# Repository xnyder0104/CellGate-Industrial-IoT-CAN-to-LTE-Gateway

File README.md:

# CellGate: Industrial IoT CAN-to-LTE Gateway

## Project Overview

This project is a compact, reliable, and manufacturable 2-layer custom PCB designed to bridge physical CAN bus networks with cloud infrastructure via cellular telemetry. Operating in harsh embedded environments, such as automotive engine bays or industrial factory floors, requires highly robust hardware. Power fluctuations, electrical noise, and Electrostatic Discharge (ESD) events can easily destroy standard development boards or cause critical communication failures.

To overcome these challenges, CellGate utilizes an STM32 ARM Cortex-M0+ microcontroller paired with a Quectel EC200U LTE Cat-1 module to handle high-speed data processing and transmission. The board integrates an industrial power path, strictly isolated voltage domains, multi-stage hardware protection, and a seamless load-sharing battery backup system, ensuring uninterrupted diagnostic data flow.

## Key Features & Engineering Highlights

* **Advanced Power Path Management:** Implements a PMV65XP MOSFET-based load-sharing architecture that automatically and seamlessly switches between a high-voltage external DC input (up to 40V) and a Lithium-ion battery backup without resetting the system.
* **Strict Voltage Domain Isolation:** A TXB0104 bidirectional logic level shifter protects the sensitive 1.8V Quectel silicon from the 3.3V STM32 logic signals, enabling safe, high-speed full-duplex UART transmission.
* **Fail-Safe Boot Design:** Integrates a hardware-level 10k-ohm pull-down resistor on the STM32 BOOT0 (PA14) pin to prevent the MCU from accidentally entering DFU Bootloader Mode due to ambient electrical noise during battery-only field operation.
* **Multi-Stage ESD Armor:** Deploys hardware protection across all external interfaces, including PESD2CAN TVS diodes on the differential bus lines and USBLC6 protection on the Type-C port.
* **Selectable Bus Termination:** Includes a physical jumper header for selectable 120-ohm CAN bus termination, making the board adaptable for end-of-line or mid-bus installations.
* **Comprehensive Diagnostic UI:** A dedicated 9-LED onboard panel provides immediate visual debugging for Main Power, Battery Charging, Battery Full, MCU Status, LTE Network Status, GPS Fix, CAN Activity, UART Activity, and Hardware Errors/Faults.

## Hardware Architecture & Working Principle

### 1. Power Supply & Battery Protection (+V_SYS)
* **HV Step-Down:** An LMR14030 buck converter steps down raw industrial inputs (up to 40V) to a stable 5V rail.
* **Voltage Regulation:** The master +V_SYS net feeds two independent LDOs: an AMS1117 generating the 3.3V MCU domain, and a TLV70218 generating the 1.8V modem reference domain.
* **Battery Circuitry:** A TP4056 linear charger manages Li-ion charging. It is paired with a strictly low-side DW01A controller and dual FS8205A MOSFETs, which continuously monitor the cell and isolate the battery ground instantly if over-charge, over-discharge, or a dead-short is detected.

### 2. Core Processing & Connectivity
* **Microcontroller Logic:** The STM32G0B1CBT6 handles all data preprocessing, CAN-to-UART conversion, and LED status mapping. 
* **Cellular & GNSS:** The Quectel EC200U module executes AT commands for LTE telemetry and GNSS location tracking. It is powered directly from the high-current battery rail (+V_BAT) to sustain 2-Amp transmission bursts safely.
* **CAN Interface:** An SN65HVD230 transceiver safely translates high-voltage automotive differential CAN signals down to the 3.3V logic level required by the STM32.

### 3. Debugging & Firmware Interfaces
* **SWD Programming:** Standard 5-pin SWD interface (SWDIO, SWCLK, NRST, +3.3V, GND) for flashing the STM32.
* **Hardware UART:** An exposed 4-pin hardware UART header operating strictly at 1.8V (VDD_EXT) for direct, low-level Quectel modem diagnostics.
* **USB Type-C:** Directly exposes the EC200U USB interface for cellular firmware upgrades and advanced module diagnostics.

## PCB Layout & Manufacturing Strategy

The board was meticulously routed as a 2-layer PCB, optimizing for low parasitic inductance, signal integrity, and manufacturability:

* **Solid Ground Plane:** The entire bottom layer is maintained as an unbroken solid copper ground plane to absorb the massive switching noise of the LMR14030 buck converter and provide a clean return path for RF signals.
* **Bottom-Layer Decoupling:** To minimize trace length and parasitic inductance, critical decoupling capacitors for the STM32 and Quectel EC200U are placed directly underneath the component pins on the bottom layer, fed by localized via stitching.
* **45-Degree Mitered Routing:** All high-speed data lines (6-mil trace width) utilize clean 45-degree cornering, avoiding 90-degree right angles and acute acid traps to ensure perfect chemical etching during manufacturing.
* **RF Trace Geometry:** 50-ohm controlled impedance traces are routed cleanly from the modem RF pads directly to the U.FL edge connectors, completely avoiding vias to prevent signal reflection.

## Applications

* Heavy machinery and fleet management telemetry (CAN bus diagnostics).
* Remote industrial equipment monitoring and predictive maintenance.
* Standalone IoT sensor gateways for off-grid environmental tracking.
* High-reliability telemetry nodes requiring uninterruptible power supplies (UPS).

## Future Scope

* **Mechanical Enclosure Design:** Utilizing the exported 3D .step files to design a custom, IP67-rated waterproof housing for harsh outdoor deployments.
* **Firmware Over-The-Air (FOTA):** Implementing a custom MCU bootloader to download, verify, and flash firmware updates seamlessly via the Quectel LTE connection.
* **Onboard Sensor Expansion:** Integrating standard I2C/SPI environmental sensors (e.g., temperature, humidity, accelerometer) directly onto the motherboard for localized physical diagnostics.

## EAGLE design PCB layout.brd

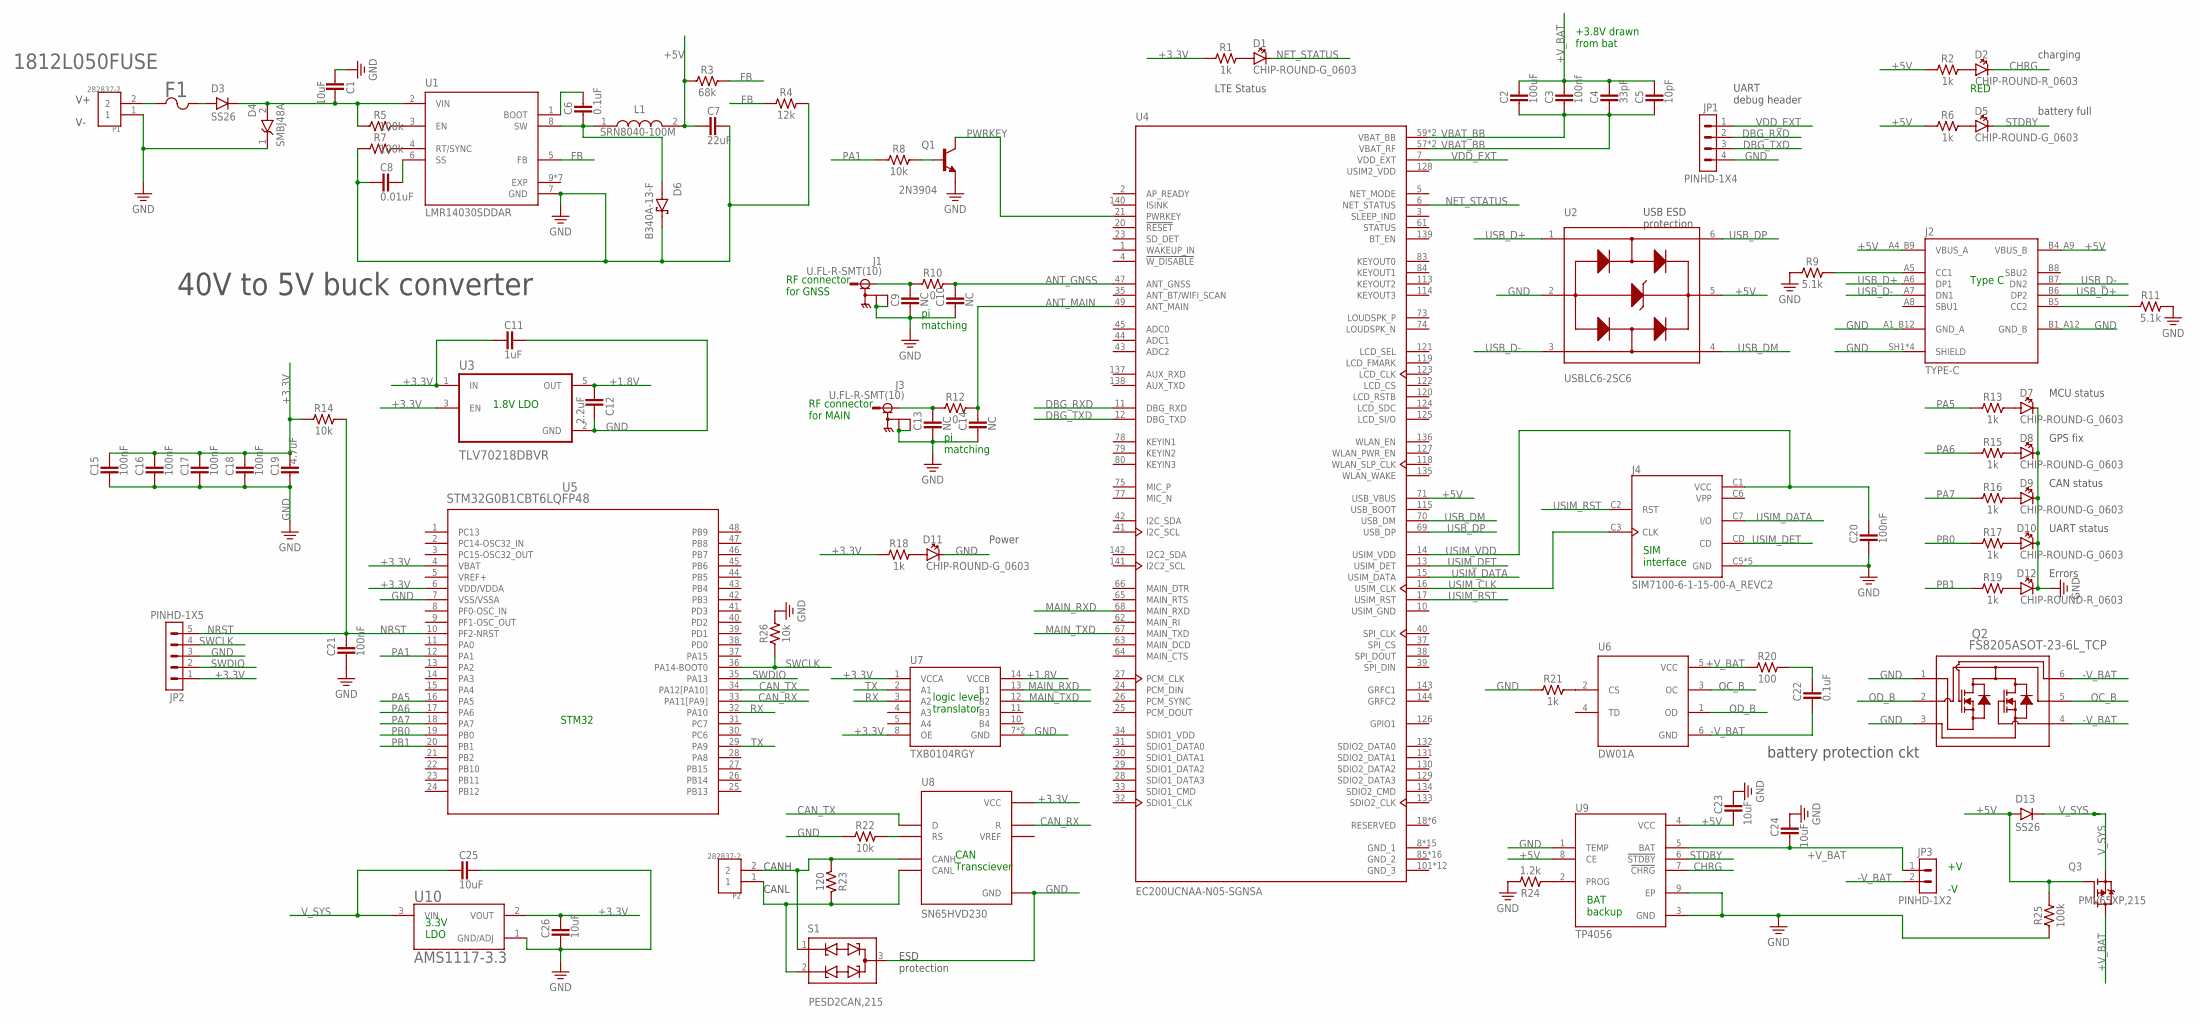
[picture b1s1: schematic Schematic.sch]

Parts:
C1, C23, C24, C25, C26: 10uF; CAPC1005X60
C2: 100uF; CAPC1608X85
C3: 100nf; CAPC1608X85
C4: 33pF; CAPC1608X85
C5: 10pF; CAPC1608X85
C6, C22: 0.1uF; CAPC1005X60
C7: 22uF; CAPC1005X60
C8: 0.01uF; CAPC1005X60
C9, C10, C13, C14: NC; CAPC1005X60
C11: 1uF; CAPC1005X60
C12: 2.2uF; CAPC1005X60
C15, C16, C17, C18, C20, C21: 100nF; CAPC1005X60
C19: 4.7uF; CAPC1005X60
D1, D5, D7, D8, D9, D10, D11: CHIP-ROUND-G_0603; LEDC1608X65N_RND-G
D2, D12: CHIP-ROUND-R_0603; LEDC1608X65N_RND-R
D3, D13: SS26
D4: SMBJ48A; DIOM5436X261N
D6: B340A-13-F; DIOM5226X240N
F1: 1812L050FUSE; FUSE_1812L05060_LTF
J1, J3: U.FL-R-SMT(10); HIROSE_U.FL-R-SMT(10)
J2: TYPE-C; SHOUHAN_TYPE-C_16PIN_2MD_(073)
J4: SIM7100-6-1-15-00-A_REVC2; GCT_SIM7100-6-1-15-00-A_REVC2
JP1: PINHD-1X4; 1X04
JP2: PINHD-1X5; 1X05
JP3: PINHD-1X2; 1X02
L1: SRN8040-100M; SRN8040100M
P1, P2: 282837-2; TE_282837-2
Q1: 2N3904; TO92127P495H495-3
Q2: FS8205ASOT-23-6L_TCP; SOT-23-6L_TCP
Q3: PMV65XP,215; SOT95P230X110-3N
R1, R2, R6, R13, R15, R16, R17, R18, R19, R21: 1k; RESC1005X40
R3: 68k; RESC1005X40
R4: 12k; RESC1005X40
R5, R7, R25: 100k; RESC1005X40
R8, R14, R22, R26: 10k; RESC1005X40
R9, R11: 5.1k; RESC1005X40
R10, R12: 0; RESC1005X40
R20: 100; RESC1005X40
R23: 120; RESC1005X40
R24: 1.2k; RESC1005X40
S1: PESD2CAN,215; DIO_PESD2CAN,215
U1: LMR14030SDDAR; SOIC127P600X170-9N
U2: USBLC6-2SC6; SOT95P280X145-6N
U3: TLV70218DBVR; SOT95P280X145-5N
U4: EC200UCNAA-N05-SGNSA; XCVR_EC200UCNAA-N05-SGNSA
U5: STM32G0B1CBT6LQFP48; LQFP48_STM32G0B1CBT_STM
U6: DW01A; SOT95P280X145-6N
U7: TXB0104RGY; S-PVQFN-N14
U8: SN65HVD230; SOIC127P599X175-8N
U9: TP4056; SOP127P600X175-9N
U10: AMS1117-3.3; SOT229P700X180-4N

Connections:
+1.8V: C12.2, U3.5 (OUT), U7.14 (VCCB)
+3.3V: C11.2, C15.1, C16.1, C17.1, C18.1, C19.1, C26.1, JP2.1, R1.1, R14.1, R18.1, U3.1 (IN), U3.3 (EN), U5.4 (VBAT), U5.6 (VDD/VDDA), U7.1 (VCCA), U7.8 (OE), U8.3 (VCC), U10.2 (VOUT)
+5V: C7.2, C23.2, D13.A, J2.A4_B9 (VBUS_A), J2.B4_A9 (VBUS_B), L1.2, Q3.1 (G), R2.1, R3.1, R6.1, R25.2, U2.5 (VBUS), U4.71 (USB_VBUS), U9.4 (VCC), U9.8 (CE)
+V_BAT: C2.1, C3.1, C4.1, C5.1, C24.2, JP3.1, Q3.3 (D), R20.1, U6.5 (VCC), U9.5 (BAT)
-V_BAT: C22.2, JP3.2, Q2.4, Q2.6, U6.6 (GND)
ANT_GNSS: C10.1, R10.2, U4.47 (ANT_GNSS)
ANT_MAIN: C14.1, R12.2, U4.49 (ANT_MAIN)
CANH: P2.2, R23.2, S1.1 (C1), U8.7 (CANH)
CAN_RX: U5.33 (PA11[PA9]), U8.4 (R)
CAN_TX: U5.34 (PA12[PA10]), U8.1 (D)
CHRG: D2.C, U9.7 (!CHRG)
DBG_RXD: JP1.2, U4.11 (DBG_RXD)
DBG_TXD: JP1.3, U4.12 (DBG_TXD)
EXP: U1.9 (EXP), U1.V1 (EXP), U1.V2 (EXP), U1.V3 (EXP), U1.V4 (EXP), U1.V5 (EXP), U1.V6 (EXP)
FB: R3.2, R4.1, U1.5 (FB)
GND: C1.2, C7.1, C8.2, C9.2, C10.2, C11.1, C12.1, C13.2, C14.2, C15.2, C16.2, C17.2, C18.2, C19.2, C20.2, C21.2, C23.1, C24.1, C25.1, C26.2, D4.1 (K), D6.C, D7.C, D8.C, D9.C, D10.C, D11.C, D12.C, J1.G1, J1.G2, J2.A1_B12 (GND_A), J2.B1_A12 (GND_B), J2.SH1 (SHIELD), J2.SH2 (SHIELD), J2.SH3 (SHIELD), J2.SH4 (SHIELD), J3.G1, J3.G2, J4.C5 (GND), J4.G1 (GND), J4.G2 (GND), J4.G3 (GND), J4.G4 (GND), JP1.4, JP2.3, P1.1, Q1.1 (E), Q2.1, Q2.3, R4.2, R7.1, R9.1, R11.2, R21.1, R22.1, R24.2, R25.1, R26.2, S1.3 (CC), U1.7 (GND), U2.2 (GND), U3.2 (GND), U5.7 (VSS/VSSA), U7.7 (GND), U7.THERMALPAD (GND), U8.2 (GND), U9.1 (TEMP), U9.3 (GND), U9.9 (EP), U10.1 (GND/ADJ)
GND_1: U4.8 (GND_1), U4.9 (GND_1), U4.19 (GND_1), U4.22 (GND_1), U4.36 (GND_1), U4.46 (GND_1), U4.48 (GND_1), U4.50 (GND_1), U4.51 (GND_1), U4.52 (GND_1), U4.53 (GND_1), U4.54 (GND_1), U4.56 (GND_1), U4.72 (GND_1), U4.76 (GND_1)
GND_2: U4.85 (GND_2), U4.86 (GND_2), U4.87 (GND_2), U4.88 (GND_2), U4.89 (GND_2), U4.90 (GND_2), U4.91 (GND_2), U4.92 (GND_2), U4.93 (GND_2), U4.94 (GND_2), U4.95 (GND_2), U4.96 (GND_2), U4.97 (GND_2), U4.98 (GND_2), U4.99 (GND_2), U4.100 (GND_2)
GND_3: U4.101 (GND_3), U4.102 (GND_3), U4.103 (GND_3), U4.104 (GND_3), U4.105 (GND_3), U4.106 (GND_3), U4.107 (GND_3), U4.108 (GND_3), U4.109 (GND_3), U4.110 (GND_3), U4.111 (GND_3), U4.112 (GND_3)
MAIN_RXD: U4.68 (MAIN_RXD), U7.13 (B1)
MAIN_TXD: U4.67 (MAIN_TXD), U7.12 (B2)
unnamed: Q1.2 (B), R8.2
unnamed: J2.A5 (CC1), R9.2
unnamed: J2.B5 (CC2), R11.1
unnamed: C9.1, J1.SIG, R10.1
unnamed: R24.1, U9.2 (PROG)
unnamed: D2.A, R2.2
unnamed: D5.A, R6.2
unnamed: C13.1, J3.SIG, R12.1
unnamed: R22.2, U8.8 (RS)
unnamed: F1.1, P1.2
unnamed: D3.A, F1.2
unnamed: C1.1, D3.C, D4.2 (A), R5.1, U1.2 (VIN)
unnamed: C6.1, U1.1 (BOOT)
unnamed: C6.2, D6.A, L1.1, U1.8 (SW)
unnamed: R5.2, U1.3 (EN)
unnamed: R7.2, U1.4 (RT/SYNC)
unnamed: C8.1, U1.6 (SS)
unnamed: R21.2, U6.2 (CS)
unnamed: D11.A, R18.2
unnamed: C22.1, R20.2
unnamed: P2.1, R23.1, S1.2 (C2), U8.6 (CANL)
unnamed: D1.A, R1.2
unnamed: D7.A, R13.2
unnamed: D8.A, R15.2
unnamed: D9.A, R16.2
unnamed: D10.A, R17.2
unnamed: D12.A, R19.2
NET_STATUS: D1.C, U4.6 (NET_STATUS)
NRST: C21.1, JP2.5, R14.2, U5.10 (PF2-NRST)
OC_B: Q2.5, U6.3 (OC)
OD_B: Q2.2, U6.1 (OD)
PA1: R8.1, U5.12 (PA1)
PA5: R13.1, U5.16 (PA5)
PA6: R15.1, U5.17 (PA6)
PA7: R16.1, U5.18 (PA7)
PB0: R17.1, U5.19 (PB0)
PB1: R19.1, U5.20 (PB1)
PWRKEY: Q1.3 (C), U4.21 (PWRKEY)
RX: U5.32 (PA10), U7.3 (A2)
SDIO1_VDD: U4.34 (SDIO1_VDD)
STDBY: D5.C, U9.6 (!STDBY)
SWCLK: JP2.4, R26.1, U5.36 (PA14-BOOT0)
SWDIO: JP2.2, U5.35 (PA13)
TX: U5.29 (PA9), U7.2 (A1)
USB_D+: J2.A6 (DP1), J2.B6 (DP2), U2.1 (I/O1_IN)
USB_D-: J2.A7 (DN1), J2.B7 (DN2), U2.3 (I/O2_IN)
USB_DM: U2.4 (I/O2_OUT), U4.70 (USB_DM)
USB_DP: U2.6 (I/O1_OUT), U4.69 (USB_DP)
USIM2_VDD: U4.128 (USIM2_VDD)
USIM_CLK: J4.C3 (CLK), U4.16 (USIM_CLK)
USIM_DATA: J4.C7 (I/O), U4.15 (USIM_DATA)
USIM_DET: J4.CD, U4.13 (USIM_DET)
USIM_GND: U4.10 (USIM_GND)
USIM_RST: J4.C2 (RST), U4.17 (USIM_RST)
USIM_VDD: C20.1, J4.C1 (VCC), U4.14 (USIM_VDD)
VBAT_BB: C2.2, C3.2, C4.2, C5.2, U4.57 (VBAT_RF), U4.58 (VBAT_RF), U4.59 (VBAT_BB), U4.60 (VBAT_BB)
VDD_EXT: JP1.1, U4.7 (VDD_EXT)
VPP: J4.C6 (VPP)
VREF+: U5.5 (VREF+)
V_SYS: C25.2, D13.C, Q3.2 (S), U10.3 (VIN)

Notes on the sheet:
1.8V LDO
logic level translator
CAN Transciever
STM32
Type C
RF connector for GNSS
pi matching
SIM interface
BAT backup
RED
RF connector for MAIN
+3.8V drawn from bat
3.3V LDO
ESD protection
40V to 5V buck converter
battery protection ckt
CANH
CANL
USB ESD protection
charging
battery full
Power
LTE Status
MCU status
GPS fix
CAN status
UART status
Errors
UART debug header

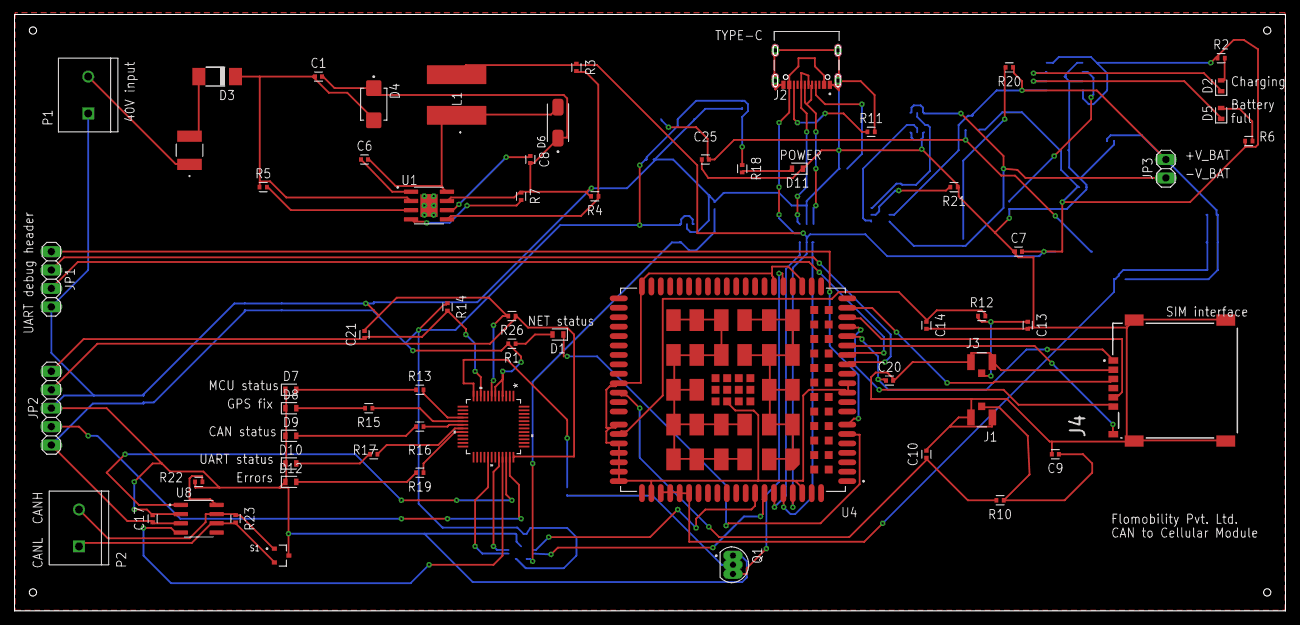
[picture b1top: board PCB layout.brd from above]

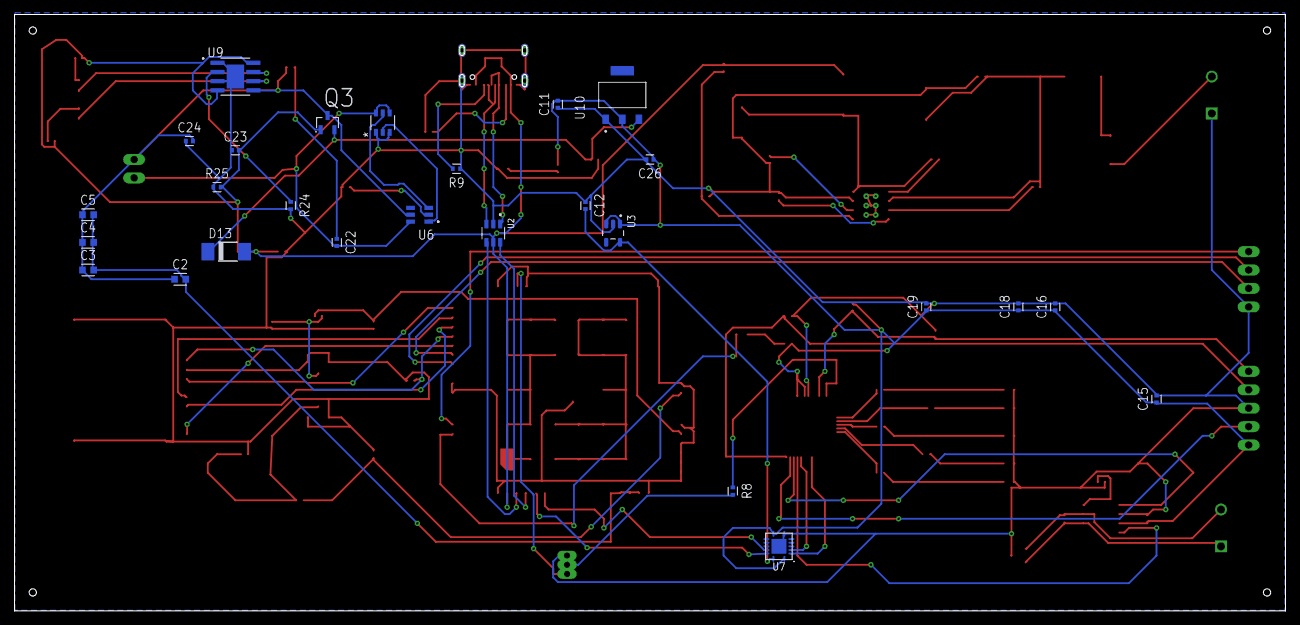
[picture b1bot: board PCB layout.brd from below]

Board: 2 copper layers, 175.2 x 82.2 mm, 90 parts (27 on the bottom side), 76 nets.

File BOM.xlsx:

Reference Designators | Quantity | Description | Package | Value | Top/Bottom
 | 1 | Board | Board
C1, C25 | 2 | Capacitor - Generic | CAPC1005X60 | 10uF | Top
C23, C24, C26 | 3 | Capacitor - Generic | CAPC1005X61 | 10uF | Bottom
C2 | 1 | Capacitor - Generic | CAPC1608X85 | 100uF | Bottom
C3 | 1 | Capacitor - Generic | CAPC1608X85 | 100nf | Bottom
C4 | 1 | Capacitor - Generic | CAPC1608X85 | 33pF | Bottom
C5 | 1 | Capacitor - Generic | CAPC1608X85 | 10pF | Bottom
C22 | 1 | Capacitor - Generic | CAPC1005X60 | 0.1uF | Bottom
C6 | 1 | Capacitor - Generic | CAPC1005X60 | 0.1uF | Top
C7 | 1 | Capacitor - Generic | CAPC1005X60 | 22uF | Top
C8 | 1 | Capacitor - Generic | CAPC1005X60 | 0.01uF | Top
C9, C10, C13, C14 | 4 | Capacitor - Generic | CAPC1005X60 | NC | Top
C11 | 1 | Capacitor - Generic | CAPC1005X60 | 1uF | Bottom
C12 | 1 | Capacitor - Generic | CAPC1005X60 | 2.2uF | Bottom
C15, C16, C18 | 3 | Capacitor - Generic | CAPC1005X60 | 100nF | Bottom
C17, C20, C21 | 3 | Capacitor - Generic | CAPC1005X61 | 100nF | Top
C19 | 1 | Capacitor - Generic | CAPC1005X60 | 4.7uF | Bottom
D1, D5, D7, D8, D9, D10, D11 | 7 | Green LED - Generic | LEDC1608X65N_RND-G | CHIP-ROUND-G_0603 | Top
D2, D12 | 2 | Red LED - Generic | LEDC1608X65N_RND-R | CHIP-ROUND-R_0603 | Top
D3 | 1 | Schottky Diode | SS26 | SS26 | Top
D13 | 1 | Schottky Diode | SS26 | SS26 | Bottom
D4 | 1 | 600-watt TVS diode | DIOM5436X261N | SMBJ48A | Top
D6 | 1 | B340A-13-F | DIOM5226X240N | B340A-13-F | Top
F1 | 1 | Polymeric positive temperature coefficient (PPTC) resettable fuse | FUSE_1812L05060_LTF | 1812L050FUSE | Top
J1, J3 | 2 | RF connector receptacle | HIROSE_U.FL-R-SMT(10) | U.FL-R-SMT(10) | Top
J2 | 1 | Female USB Type-C receptacle | SHOUHAN_TYPE-C_16PIN_2MD_(073) | TYPE-C | Top
J4 | 1 | micro SIM card connector | GCT_SIM7100-6-1-15-00-A_REVC2 | SIM7100-6-1-15-00-A_REVC2 | Top
JP1 | 1 | Pin Header | 1X04 | PINHD-1X4 | Top
JP2 | 1 | Pin Header | 1X05 | PINHD-1X5 | Top
JP3 | 1 | Pin Header | 1X02 | PINHD-1X2 | Top
L1 | 1 | Bourns SRN8040 Series Type SMD Shielded Wire-wound SMD Inductor with a Ferrite 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 | SRN8040100M | SRN8040-100M | Top
P1, P2 | 2 | 2-pin screw terminal | TE_282837-2 | 282837-2 | Top
Q1 | 1 | NPN BJT | TO92127P495H495-3 | 2N3904 | Top
Q2 | 1 | N-channel MOSFET | SOT-23-6L_TCP | FS8205ASOT-23-6L_TCP | Bottom
Q3 | 1 | P-channel MOSFET | SOT95P230X110-3N | PMV65XP,215 | Bottom
R1, R2, R6, R13, R15, R16, R17, R18, R19, R21 | 10 | Resistor Fixed - ANSI | RESC1005X40 | 1k | Top
R3 | 1 | Resistor Fixed - ANSI | RESC1005X40 | 68k | Top
R4 | 1 | Resistor Fixed - ANSI | RESC1005X40 | 12k | Top
R5, R7 | 2 | Resistor Fixed - ANSI | RESC1005X40 | 100k | Top
R25 | 1 | Resistor Fixed - ANSI | RESC1005X41 | 100k | Bottom
R14, R22, R26 | 3 | Resistor Fixed - ANSI | RESC1005X40 | 10k | Top
R8 | 1 | Resistor Fixed - ANSI | RESC1005X41 | 10k | Bottom
R11 | 1 | Resistor Fixed - ANSI | RESC1005X40 | 5.1k | Top
R9 | 1 | Resistor Fixed - ANSI | RESC1005X41 | 5.1k | Bottom
R10, R12 | 2 | Resistor Fixed - ANSI | RESC1005X40 | 0 | Top
R20 | 1 | Resistor Fixed - ANSI | RESC1005X40 | 100 | Top
R23 | 1 | Resistor Fixed - ANSI | RESC1005X40 | 120 | Top
R24 | 1 | Resistor Fixed - ANSI | RESC1005X40 | 1.2k | Bottom
S1 | 1 | ESD Protection for CAN | DIO_PESD2CAN,215 | PESD2CAN,215 | Top
U1 | 1 | Step-down (buck) voltage regulator | SOIC127P600X170-9N | LMR14030SDDAR | Top
U2 | 1 | ESD Protection for USB | SOT95P280X145-6N | USBLC6-2SC6 | Bottom
U3 | 1 | TLV70218DBVR | SOT95P280X145-5N | TLV70218DBVR | Bottom
U4 | 1 | EC200U | XCVR_EC200UCNAA-N05-SGNSA | EC200UCNAA-N05-SGNSA | Top
U5 | 1 | STM32 | LQFP48_STM32G0B1CBT_STM | STM32G0B1CBT6LQFP48 | Top
U6 | 1 | Battery protection IC | SOT95P280X145-6N | DW01A | Bottom
U7 | 1 | 4-bit bidirectional voltage-level translator | S-PVQFN-N14 | TXB0104RGY | Bottom
U8 | 1 | 3.3V CAN bus transceiver | SOIC127P599X175-8N | SN65HVD230 | Top
U9 | 1 | Linear charger IC | SOP127P600X175-9N | TP4056 | Bottom
U10 | 1 | Linear voltage regulator IC that steps down a higher DC voltage (up to 15V) to 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 | SOT229P700X180-4N | AMS1117-3.3 | Bottom

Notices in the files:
parts and their libraries:
COPYRIGHT: Copyright (C) 2026 Ultra Librarian. All rights reserved.
